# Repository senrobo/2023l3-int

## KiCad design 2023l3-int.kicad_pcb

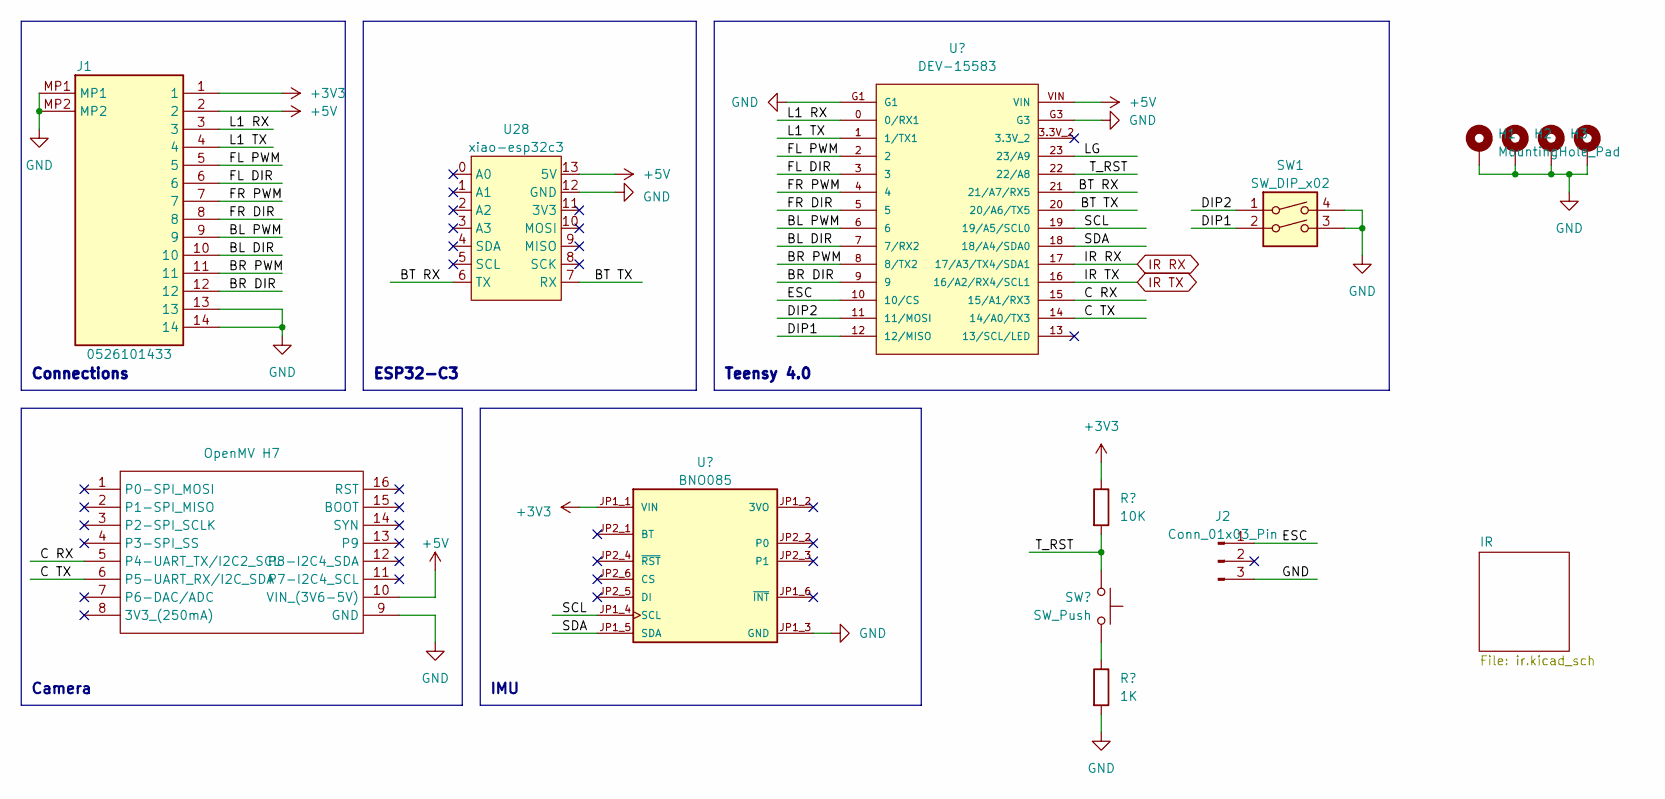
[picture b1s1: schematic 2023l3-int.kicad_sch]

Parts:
H1, H2, H3, H4: MountingHole_Pad; MountingHole_3.2mm_M3_Pad_Via
J1: 0526101433; 522711479; Manufacturer_Part_Number 52271-1479; Mouser Part Number 538-52271-1479
J2: Conn_01x03_Pin; PinHeader_1x03_P2.54mm_Vertical
R3: 10K; res0603
R5: 1K; res0603
SW1: SW_DIP_x02; SW_DIP_SPSTx02_Slide_6.7x6.64mm_W8.61mm_P2.54mm_LowProfile
SW2: SW_Push; SW_PUSH_SPST
U1: DEV-15583; teensy4
U2: OpenMV H7; openmv
U3: BNO085; bno085; PARTREV 2021-03-16
U28: xiao-esp32c3

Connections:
+3V3: J1.1, R3.1, U3.JP1_1 (VIN); also elsewhere on the board
+5V: J1.2, U1.VIN, U2.10 (VIN_(3V6-5V)), U28.13 (5V)
/BL DIR: J1.10, U1.7 (7/RX2)
/BL PWM: J1.9, U1.6
/BR DIR: J1.12, U1.9
/BR PWM: J1.11, U1.8 (8/TX2)
/BT RX: U1.21 (21/A7/RX5), U28.6 (TX)
/BT TX: U1.20 (20/A6/TX5), U28.7 (RX)
/C RX: U1.15 (15/A1/RX3), U2.5 (P4-UART_TX/I2C2_SCL)
/C TX: U1.14 (14/A0/TX3), U2.6 (P5-UART_RX/I2C_SDA)
/DIP1: SW1.2, U1.12 (12/MISO)
/DIP2: SW1.1, U1.11 (11/MOSI)
/ESC: J2.1, U1.10 (10/CS)
/FL DIR: J1.6, U1.3
/FL PWM: J1.5, U1.2
/FR DIR: J1.8, U1.5
/FR PWM: J1.7, U1.4
/L1 RX: J1.3, U1.0 (0/RX1)
/L1 TX: J1.4, U1.1 (1/TX1)
/LG: U1.23 (23/A9)
/SCL: U1.19 (19/A5/SCL0), U3.JP1_4 (SCL)
/SDA: U1.18 (18/A4/SDA0), U3.JP1_5 (SDA)
GND: H1.1, H2.1, H3.1, H4.1, J1.13, J1.14, J1.MP1, J1.MP2, J2.3, R5.2, SW1.3, SW1.4, U1.G1, U1.G3, U2.9 (GND), U3.JP1_3 (GND), U28.12 (GND); also elsewhere on the board
IR RX: U1.17 (17/A3/TX4/SDA1); also elsewhere on the board
IR TX: U1.16 (16/A2/RX4/SCL1); also elsewhere on the board
unnamed: R5.1, SW2.1

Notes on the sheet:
ESP32-C3
Camera
Teensy 4.0
IMU
Connections

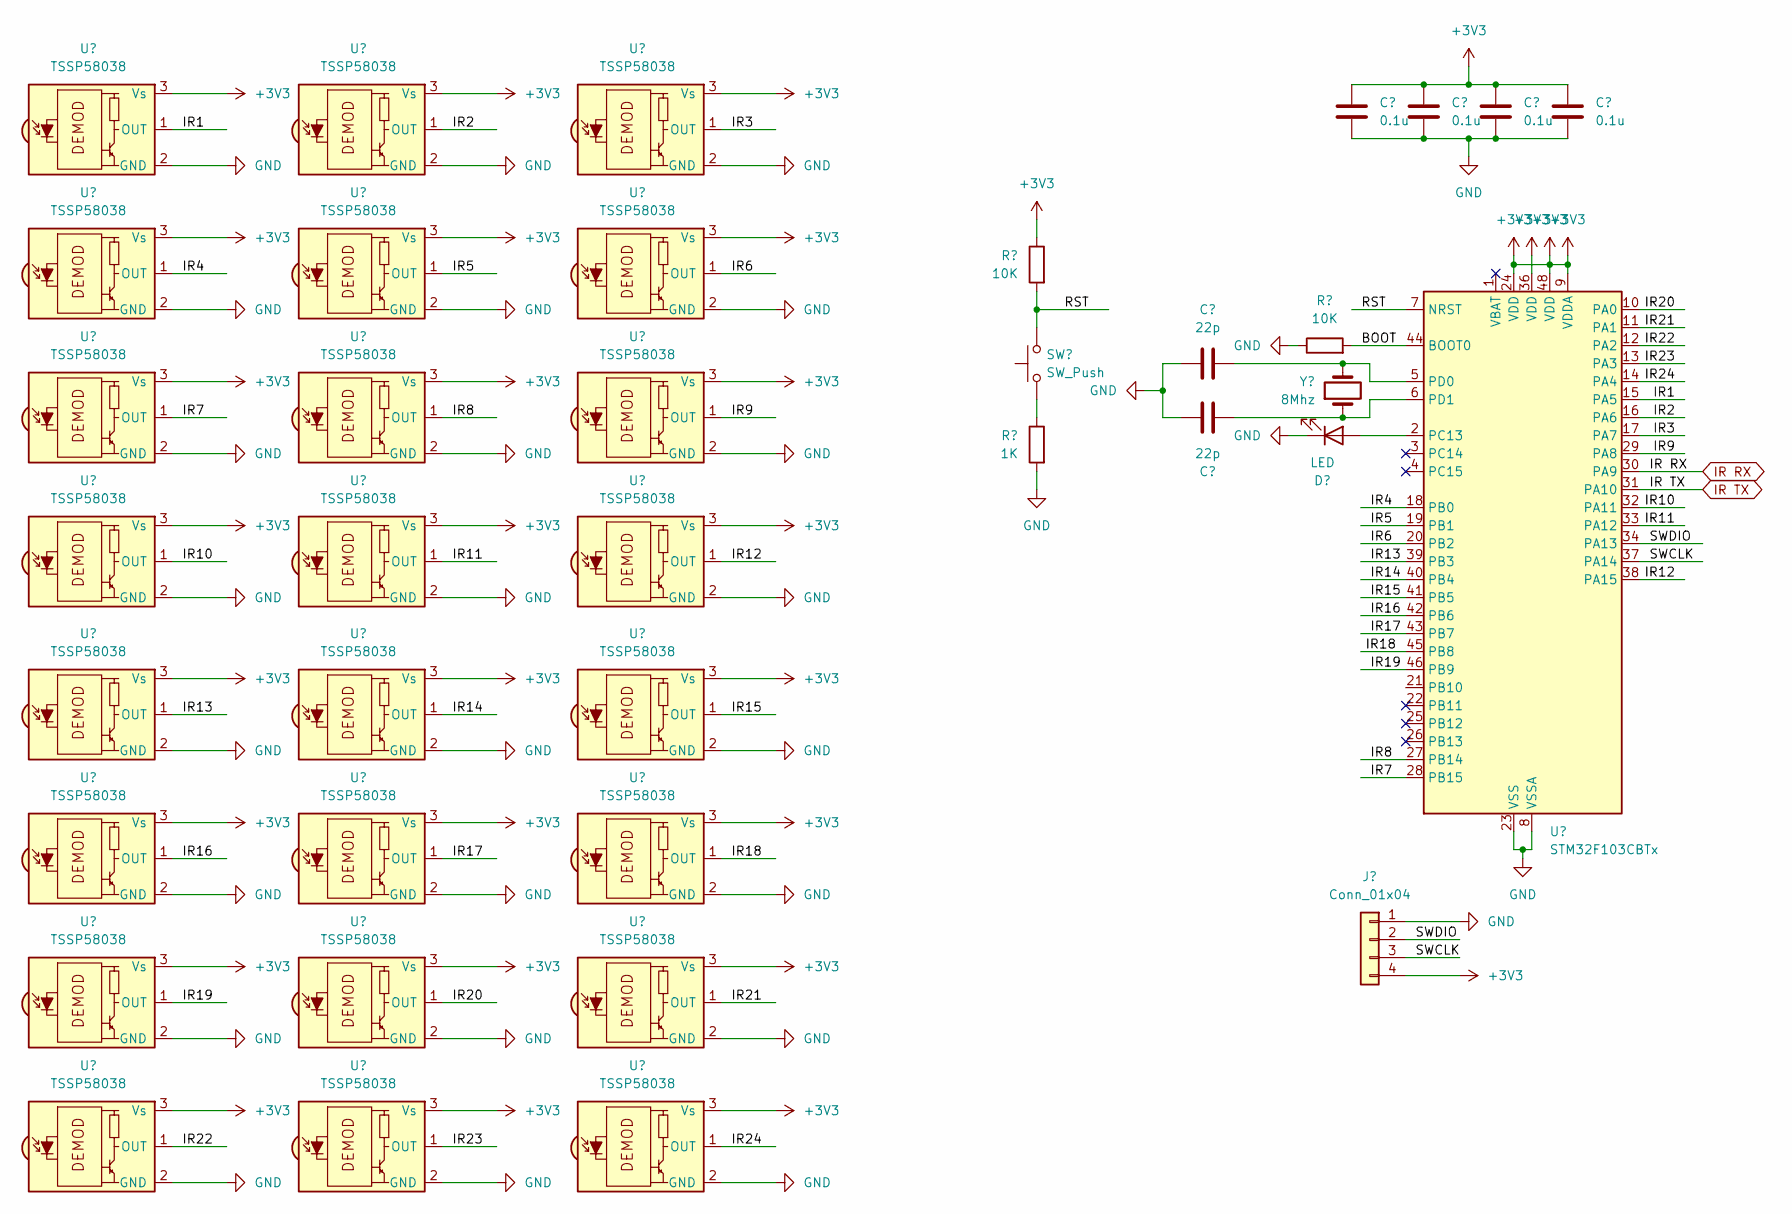
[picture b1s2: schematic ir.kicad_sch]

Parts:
C1, C2, C3, C4: 0.1u; cap0603
C5, C6: 22p; cap0603
D2: LED; led0603
IC1: STM32F103CBTx; LQFP-48_7x7mm_P0.5mm
J3: Conn_01x04; JST_SH_SM04B-SRSS-TB_1x04-1MP_P1.00mm_Horizontal
R3, R4: 10K; res0603
R5: 1K; res0603
SW2: SW_Push; SW_PUSH_SPST
U4, U5, U6, U7, U8, U9, U10, U11, U12, U13, U14, U15, U16, U17, U18, U19, U20, U21, U22, U23, U24, U25, U26, U27: TSSP58038; Vishay_MINICAST-3P
Y1: 8Mhz; Crystal

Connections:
+3V3: C1.1, C2.1, C3.1, C4.1, IC1.9 (VDDA), IC1.24 (VDD), IC1.36 (VDD), IC1.48 (VDD), J3.4, R3.1, U4.3 (Vs), U5.3 (Vs), U6.3 (Vs), U7.3 (Vs), U8.3 (Vs), U9.3 (Vs), U10.3 (Vs), U11.3 (Vs), U12.3 (Vs), U13.3 (Vs), U14.3 (Vs), U15.3 (Vs), U16.3 (Vs), U17.3 (Vs), U18.3 (Vs), U19.3 (Vs), U20.3 (Vs), U21.3 (Vs), U22.3 (Vs), U23.3 (Vs), U24.3 (Vs), U25.3 (Vs), U26.3 (Vs), U27.3 (Vs); also elsewhere on the board
/IR/BOOT: IC1.44 (BOOT0), R4.2
/IR/IR1: IC1.15 (PA5), U4.1 (OUT)
/IR/IR2: IC1.16 (PA6), U5.1 (OUT)
/IR/IR3: IC1.17 (PA7), U6.1 (OUT)
/IR/IR4: IC1.18 (PB0), U7.1 (OUT)
/IR/IR5: IC1.19 (PB1), U8.1 (OUT)
/IR/IR6: IC1.20 (PB2), U9.1 (OUT)
/IR/IR7: IC1.28 (PB15), U10.1 (OUT)
/IR/IR8: IC1.27 (PB14), U11.1 (OUT)
/IR/IR9: IC1.29 (PA8), U12.1 (OUT)
/IR/IR10: IC1.32 (PA11), U13.1 (OUT)
/IR/IR11: IC1.33 (PA12), U14.1 (OUT)
/IR/IR12: IC1.38 (PA15), U15.1 (OUT)
/IR/IR13: IC1.39 (PB3), U16.1 (OUT)
/IR/IR14: IC1.40 (PB4), U17.1 (OUT)
/IR/IR15: IC1.41 (PB5), U18.1 (OUT)
/IR/IR16: IC1.42 (PB6), U19.1 (OUT)
/IR/IR17: IC1.43 (PB7), U20.1 (OUT)
/IR/IR18: IC1.45 (PB8), U21.1 (OUT)
/IR/IR19: IC1.46 (PB9), U22.1 (OUT)
/IR/IR20: IC1.10 (PA0), U23.1 (OUT)
/IR/IR21: IC1.11 (PA1), U24.1 (OUT)
/IR/IR22: IC1.12 (PA2), U25.1 (OUT)
/IR/IR23: IC1.13 (PA3), U26.1 (OUT)
/IR/IR24: IC1.14 (PA4), U27.1 (OUT)
/IR/SWCLK: IC1.37 (PA14), J3.3
/IR/SWDIO: IC1.34 (PA13), J3.2
GND: C1.2, C2.2, C3.2, C4.2, C5.2, C6.2, D2.1 (K), IC1.8 (VSSA), IC1.23 (VSS), IC1.35 (VSS), IC1.47 (VSS), J3.1, R4.1, R5.2, U4.2 (GND), U5.2 (GND), U6.2 (GND), U7.2 (GND), U8.2 (GND), U9.2 (GND), U10.2 (GND), U11.2 (GND), U12.2 (GND), U13.2 (GND), U14.2 (GND), U15.2 (GND), U16.2 (GND), U17.2 (GND), U18.2 (GND), U19.2 (GND), U20.2 (GND), U21.2 (GND), U22.2 (GND), U23.2 (GND), U24.2 (GND), U25.2 (GND), U26.2 (GND), U27.2 (GND); also elsewhere on the board
IR RX: IC1.30 (PA9); also elsewhere on the board
IR TX: IC1.31 (PA10); also elsewhere on the board
unnamed: D2.2 (A), IC1.2 (PC13)
unnamed: C5.1, IC1.5 (PD0), Y1.2
unnamed: C6.1, IC1.6 (PD1), Y1.1
unnamed: R5.1, SW2.1

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
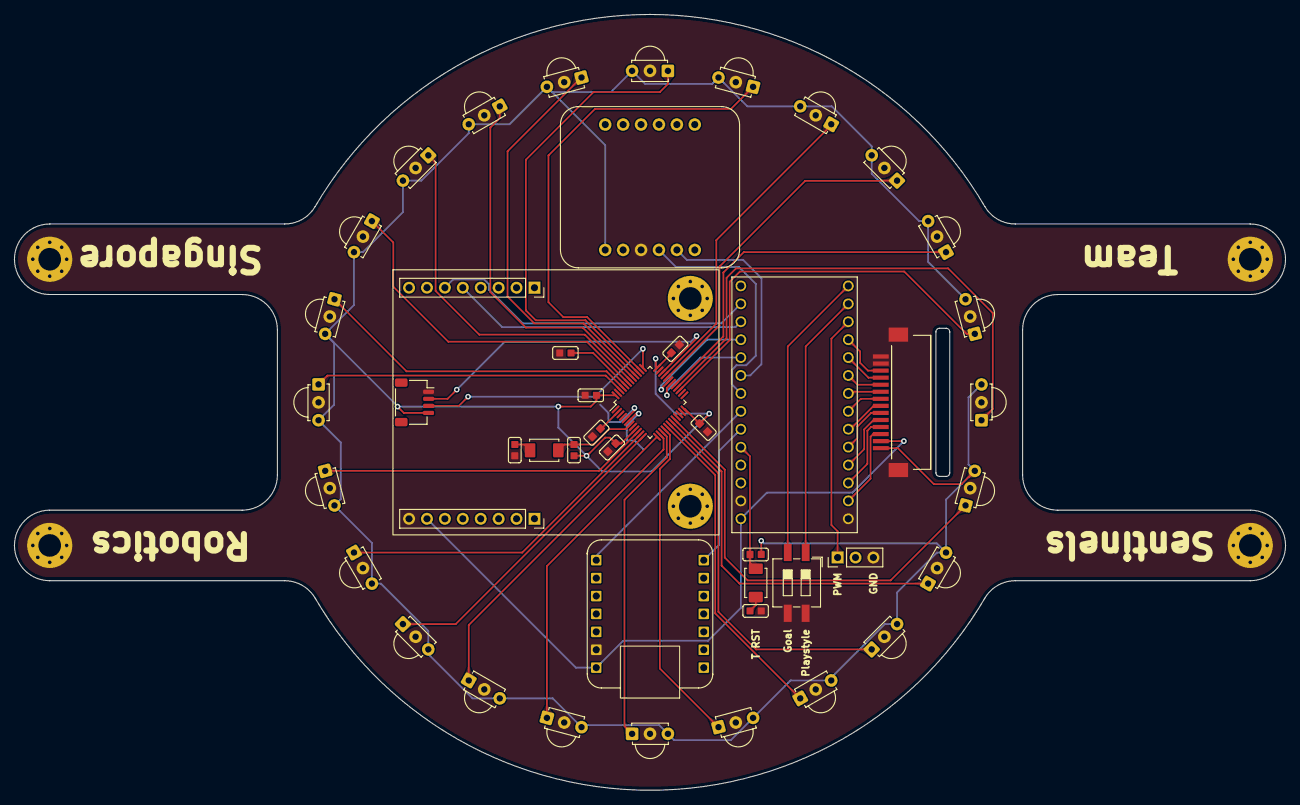
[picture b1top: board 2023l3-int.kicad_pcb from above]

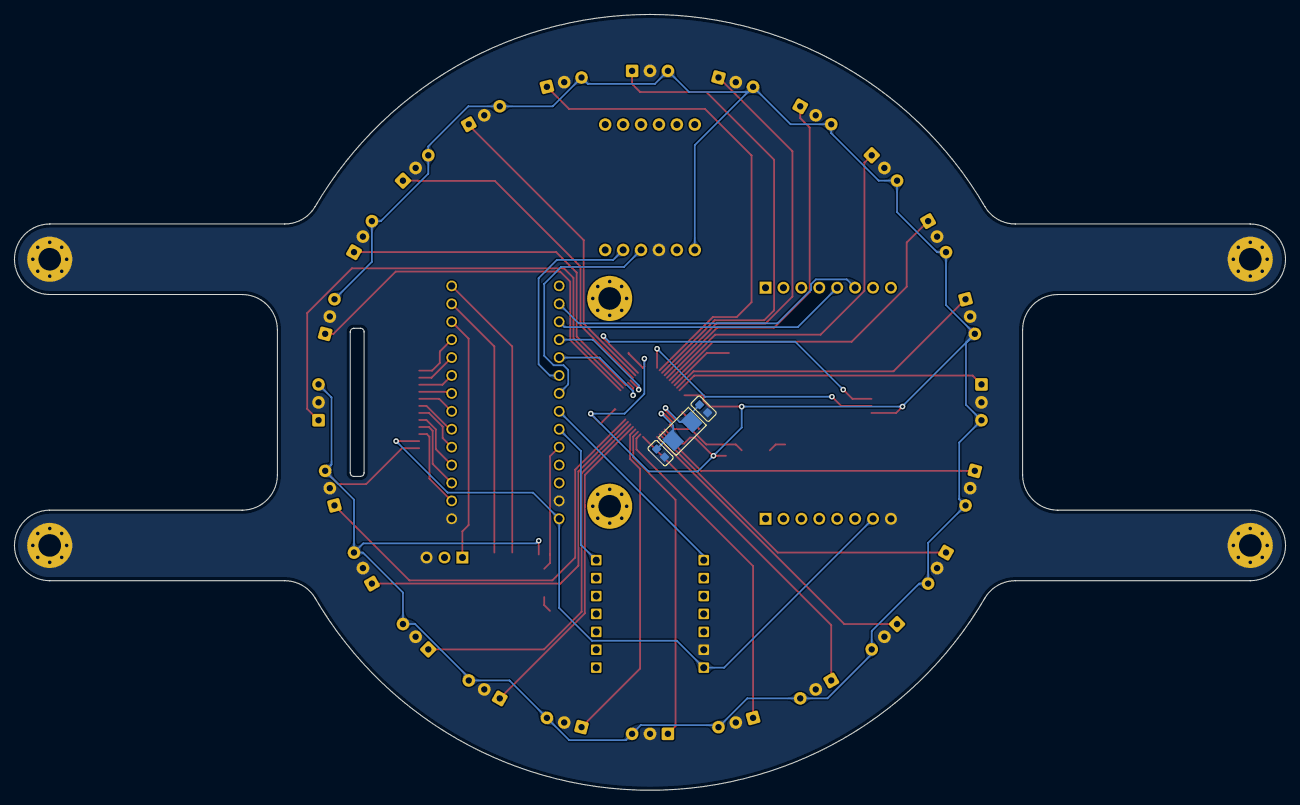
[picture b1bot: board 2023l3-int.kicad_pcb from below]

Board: 2 copper layers, 180.2 x 110.0 mm, 52 parts (3 on the bottom side), 58 nets.

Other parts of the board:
R1: 10K; res0603
R2: 1K; res0603
SW3: SW_Push; SW_PUSH_SPST

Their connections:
+3V3: R1.1; also elsewhere on the board
GND: R2.2; also elsewhere on the board
unnamed: R2.1, SW3.1

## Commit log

2023-04-26 init push
2023-05-01 formatted sch
2023-05-08 cleaned stuff
2023-05-13 placement done
2023-05-13 shit forgot to pull
2023-05-13 thank god there is version history
2023-05-13 3d pcb
2023-05-13 extra extension
2023-05-14 left with power and sw
2023-05-14 i wanna kill myself
2023-05-17 kill me
2023-05-18 decals done
2023-05-18 updated pdf
2023-05-20 oui oui
2023-05-20 reee
2023-05-20 done
2023-05-21 silkscreen
2023-05-21 drc errors
2023-05-21 final
2023-05-22 gerber
2023-05-23 jlcpcb
